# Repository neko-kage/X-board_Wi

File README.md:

# X-board_Wi
这是一个由影猫（QQ：739622490）设计的基于Arduino Pro Micro（Leonardo）与ESP-12的开发板，同样也是由WiFi Ducky固件为主的一个USB HID注入器。详细介绍及简略教程见README

// 待补充

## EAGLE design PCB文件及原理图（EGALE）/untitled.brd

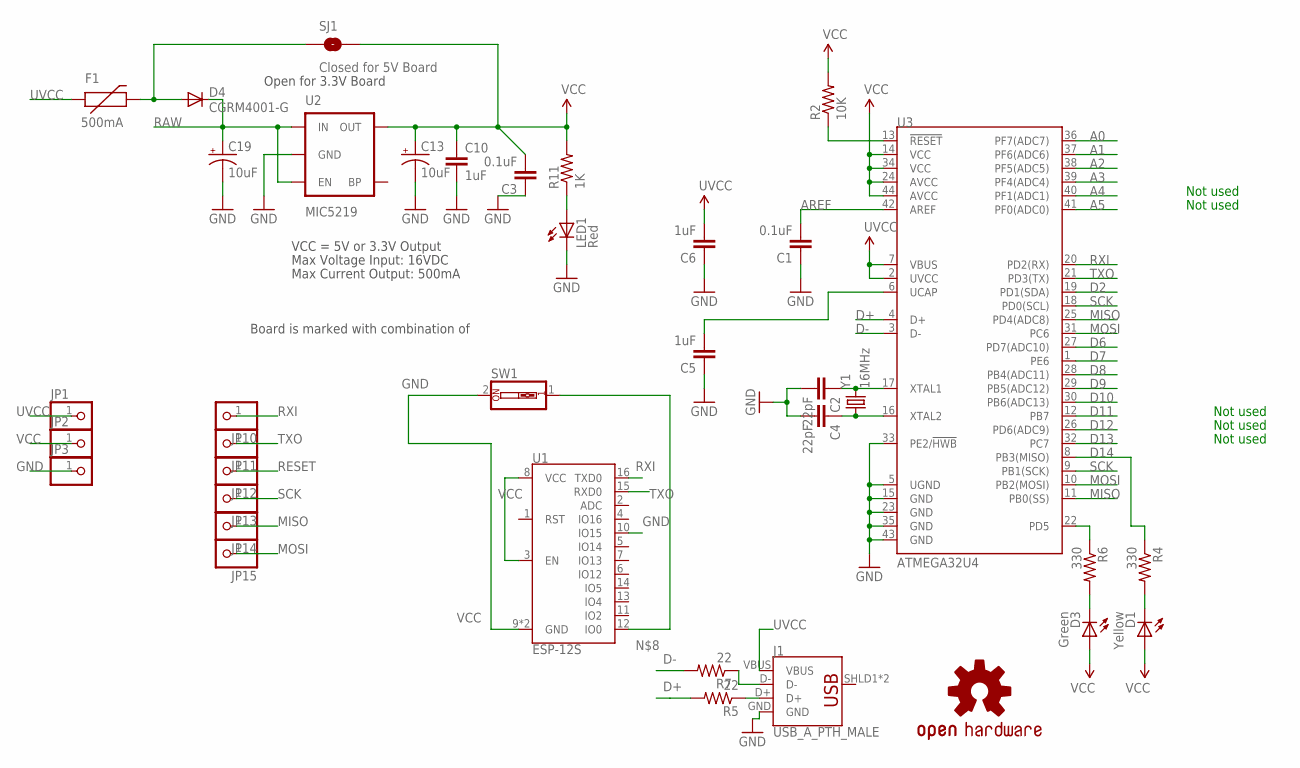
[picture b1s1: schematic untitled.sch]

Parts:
C1, C3: 0.1uF; 0603-CAP
C2, C4: 22pF; 0603-CAP
C5, C6, C10: 1uF; 0603-CAP
C13, C19: 10uF; EIA3216
D1: Yellow; LED-0603
D3: Green; LED-0603
D4: CGRM4001-G; SOD-123_MINI-SMA
F1: 500mA; PTC-1206
J1: USB_A_PTH_MALE; USB-A-H
JP1, JP2, JP3, JP10, JP11, JP12, JP13, JP14, JP15: PINHD-1X1; 1X01
LED1: Red; LED-0603
R2: 10K; 0603-RES
R4, R6: 330; 0603-RES
R5, R7: 22; 0603-RES
R11: 1K; 0603-RES
SJ1: Closed for 5V Board; SJ_2S
SW1: SW_DIP-1; EDG-01
U1: ESP-12S
U2: MIC5219; SOT23-5
U3: ATMEGA32U4; QFN-44-NOPAD_1:1-OUTFAKES
U$3: OSHW-LOGOS; OSHW-LOGO-S
Y1: 16MHz; CRYSTAL-SMD-5X3

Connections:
A0: U3.36 (PF7(ADC7))
A1: U3.37 (PF6(ADC6))
A2: U3.38 (PF5(ADC5))
A3: U3.39 (PF4(ADC4))
A4: U3.40 (PF1(ADC1))
A5: U3.41 (PF0(ADC0))
AREF: C1.2, U3.42 (AREF)
D2: U3.19 (PD1(SDA))
D6: U3.27 (PD7(ADC10))
D7: U3.1 (PE6)
D8: U3.28 (PB4(ADC11))
D9: U3.29 (PB5(ADC12))
D10: U3.30 (PB6(ADC13))
D11: U3.12 (PB7)
D12: U3.26 (PD6(ADC9))
D13: U3.32 (PC7)
D14: R4.1, U3.8 (PB3(MISO))
D+: R5.2, U3.4 (D+)
D-: R7.2, U3.3 (D-)
GND: C1.1, C2.2, C3.1, C4.2, C5.1, C6.1, C10.2, C13.C (-), C19.C (-), J1.GND, JP3.1, LED1.C, SW1.2, U1.9 (GND), U1.10 (IO15), U1.P$1 (GND), U2.2 (GND), U3.5 (UGND), U3.15 (GND), U3.23 (GND), U3.33 (PE2/!HWB), U3.35 (GND), U3.43 (GND)
MISO: JP14.1, U3.11 (PB0(SS)), U3.25 (PD4(ADC8))
MOSI: JP15.1, U3.10 (PB2(MOSI)), U3.31 (PC6)
unnamed: C4.1, U3.16 (XTAL2), Y1.1
unnamed: C2.1, U3.17 (XTAL1), Y1.3 (2)
unnamed: D4.A, F1.2, SJ1.1
unnamed: C5.2, U3.6 (UCAP)
unnamed: D1.C, R4.2
unnamed: D3.C, R6.2
unnamed: SW1.1, U1.12 (IO0)
unnamed: J1.D+, R5.1
unnamed: J1.D-, R7.1
unnamed: LED1.A, R11.1
RAW: C19.A (+), D4.C, U2.1 (IN), U2.3 (EN)
RESET: JP12.1, R2.1, U3.13 (!RESET)
RXI: JP10.1, U1.16 (TXD0), U3.20 (PD2(RX))
SCK: JP13.1, U3.9 (PB1(SCK)), U3.18 (PD0(SCL))
TXLED: R6.1, U3.22 (PD5)
TXO: JP11.1, U1.15 (RXD0), U3.21 (PD3(TX))
UVCC: C6.2, F1.1, J1.VBUS, JP1.1, U3.2 (UVCC), U3.7 (VBUS)
VCC: C3.2, C10.1, C13.A (+), D1.A, D3.A, JP2.1, R2.2, R11.2, SJ1.2, U1.3 (EN), U1.8 (VCC), U2.5 (OUT), U3.14 (VCC), U3.24 (AVCC), U3.34 (VCC), U3.44 (AVCC)

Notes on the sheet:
Max Voltage Input: 16VDC
Max Current Output: 500mA
Board is marked with combination of
VCC = 5V or 3.3V Output
Not used
Open for 3.3V Board

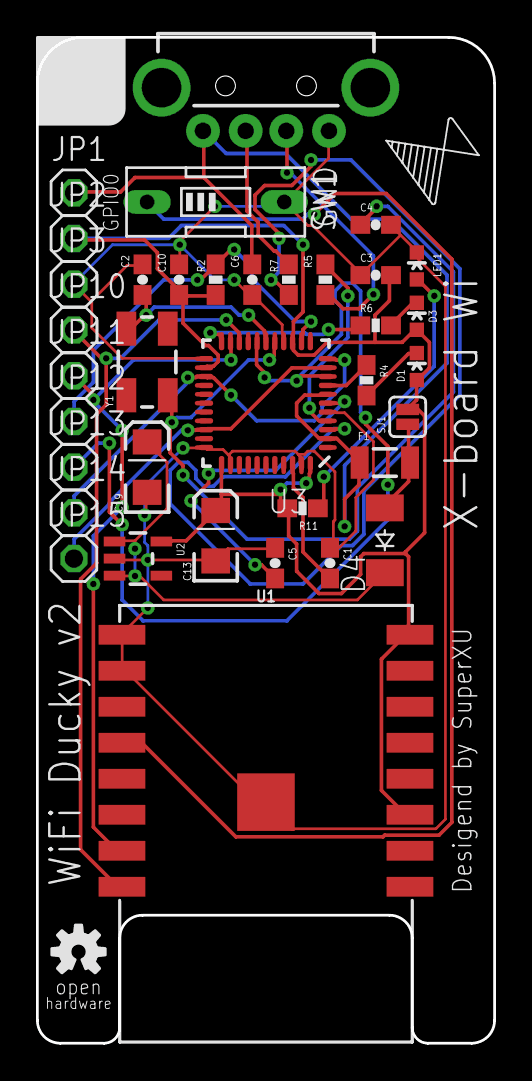
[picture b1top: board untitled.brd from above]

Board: 2 copper layers, 25.4 x 55.9 mm, 37 parts (0 on the bottom side), 25 nets.

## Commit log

2019-10-22 PCB与原理图
    V1.0版本
2019-10-30 Set theme jekyll-theme-cayman
2021-08-13 Change name

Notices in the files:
parts and their libraries:
SparkFun-Connectors: Licensing: Creative Commons ShareAlike 4.0 International - https://creativecommons.org/licenses/by-sa/4.0
